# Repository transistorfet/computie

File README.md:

Computie68k
===========

###### *Started October 03, 2019*

Computie is a series of single board computers using the 68010 and 68030 CPUs, along with a simple unix-like
operating system written in C, with preemptive multitasking via a timer interrupt provided by the 68681
serial port controller that is common to all boards.

k30-SBC is the newest board, using a surface-mount 68030 CPU, 2MB of Static RAM, 512KB of Flash for the boot
software and monitor program, and a CompactFlash slot.

68k-SBC is a single board computer with a 68010 CPU, 1MB SRAM, 1MB Flash, and a 68681 Dual UART controller.

68k-SMT is a mostly identical design using SMT and PLCC components.  A CompactFlash card slot has been added
to this version, but it is also possible to connect a simple breadboarded version to 68k-SBC.

For more details on how I got up and running, check out [Bootstrapping a Homebuilt Computer Using An Arduino](https://transistorfet.github.io/posts/2021-09-bootstrapping_with_arduino.html)

For instructions on getting a board set up and software compiled, check out [INSTALL.md](https://github.com/transistorfet/computie/blob/main/INSTALL.md)

This repository uses git submodules, and can be cloned using:
```
git clone --recurse-submodules git@github.com:transistorfet/computie.git
```

ComputieVME - The Next Generation
---------------------------------

The next iteration of this project is ComputieVME, a VME-based MC68030 CPU card, which is part of
the [Retroverse](https://github.com/transistorfet/retroverse/) project, along with a number of other
VME-based components.  The new system also runs the
[Gloworm](https://github.com/transistorfet/gloworm/) operating system.  Development is ongoing and
details can be found in the github repo or at
[jabberwocky.ca](https://jabberwocky.ca/projects/retroverse/).  I also live streamed some of the
designing and building process, with recordings available at
[youtube.com/@transistorfet](https://www.youtube.com/@transistorfet)

The Operating System (Gloworm)
------------------------------

[Gloworm](https://github.com/transistorfet/gloworm/) (now in a separate repository) is largely based on reading
Operating Systems Design and Implementation 2ed by Andrew S. Tanenbaum, although I've gone with a monolithic design, at
least for the time being, for the simplicity of it.  It can do preemptive multitasking using the 68681 timer.  It also
has an implementation of the minix version 1 filesystem, which uses RAM (through a device driver) to store the data, or
a Compact Flash card connected as an IDE device.  The second serial port can be configured as a SLIP device, with a
basic implementation of UDP and TCP through a BSD sockets-style API, and an NTP command is provided for updating the
system time on boot (when booting from disk).

The above video shows connecting over serial from a modern PC and resetting the hardware to run the monitor in ROM
which displays the welcome message.  The kernel is already loaded in RAM, so running the boot command will boot
the kernel which then starts the shell.  From the shell, some basic file operations and the ps command are shown.

The k30 Single Board Computer
-----------------------------

The k30 is the latest version, using a 68030.  It has 2MB SRAM, 512KB Flash, a 68681 Dual UART, and a CompactFlash.
It's as similar to 68k-SMT as possible while still upgrading the CPU.  It doesn't use a programmable logic device for
the glue logic as many similar projects use, instead opting for eleven 74 series logic chips.  It still manages to
use the full 32-bit data bus for RAM, but only one flash chip is used which has an 8-bit data bus in order to reduce
complexity.  Most of the software will be run from RAM, so this shouldn't be a problem.

[k30 Schematics](https://github.com/transistorfet/computie/raw/main/hardware/k30-SBC/k30-SBC.pdf)

DIP switches are used to select the time delay to use for the CompactFlash card (which is interfaced directly to the
CPU), to enable the bus error watchdog timer, and to enable/disable the cache and MMU features.

k30 Revision 2
--------------

This revision fixes the issues of the previous one.  The compact flash card can now be accessed, and the OS is able
to boot entirely from the compact flash card without issue.

k30 Revision 1
--------------

I made a mistake and used the wrong size footprint for the two 74HC253s, which only come in a 16SSOP package and not
the TSSOP package used by the other logic chips.  The footprint used were 4.9 mm wide but should have been 6.2mm.
Luckily I managed to bend the pins under the body of the chips which was enough to get all the pins touching all the
pads.  It was very tricky to solder, and there was a bridge between DS3 and ground which was very difficult to get
unstuck, but it's working now.

I also made a mistake in the DSACK signals used to terminate a memory cycle, specifically for the compact flash card.
The logic was inverted, so the card was inaccessible, and my attempts at fixing it fried the clock, although it might
have just been the crystal.  I set the project aside for a while and then made a new revision.  For details on the
issues, see the [errata](https://github.com/transistorfet/computie/raw/main/hardware/k30-SBC/revisions/k30-SBC-rev1-errata.txt)

The 68k Single Board Computer
-----------------------------

A simple single board computer using a Motorola 68010 CPU, which can connect to a host computer via USB/TTL-Serial.
It has a bus for connecting a supervisor arduino or expansion devices, but it can operate standalone using the onboard
UARTs.  It has 1MB of onboard Flash, 1MB of onboard SRAM, and a 68681 Dual UART chip with GPIO.  Some of the GPIO
pins are wired to 4 general purpose LEDs and 2 general purpose buttons.

[68k Board Schematics](https://github.com/transistorfet/computie/raw/main/hardware/68k-SBC/68kBoard.pdf)

The serial ports require external TTL-to-something conversion and are designed to be used with an FTDI USB-to-Serial
cable or adapter.  Two optional jumpers can be used to supply power to the board from one of the USB ports (only one
should be jumped at a time, and only if the onboard power supply is disconnected).  It typically takes about 365mA at
5V to power.

Two jumpers are provided to select what address the ROM will appear in (either 0x0000 or 0x2000), and whether to enable
onboard DTACK generation for address space 0x0000.  By moving the ROM to 0x2000 and disabling DTACK in 0x0000, a
connected arduino can boot the 68000 directly.

I decided to use discrete 74 Series chips for the glue logic to keep it simple and easy for others to build.  I tried
to minimize the amount of logic chips needed, so it doesn't have a watchdog timer to trigger a bus error when an
unmapped address is accessed.

It's currently clocked at 12MHz, although there seems to be an issue with the arduino's DTACK generation at that speed.
It previously was working at 10MHz on the rev0 board.

The SBC version uses all DIP packaged chips and through-hole parts.  The SMT version uses surface mount chips for the
logic and ram, and PLCC packaged chips for the rest.  A CompactFlash socket and a 74HC32 to accommodate it has been
added and the power supply has been removed, but it is otherwise the same design.

SMT Revision 1
--------------

SBC Revision 2
--------------

SBC Revision 0
--------------

This version has 64KB of EEPROM instead of Flash, and doesn't have onboard interrupt circuitry.  It started off with a
68000 CPU, but that was later upgraded to a 68010 to allow for relocatable interrupt tables when using off-board
interrupt circuitry.

I made a mistake and left out the logic for LDS/UDS in the chip select for the high and low memory chips.  When writing
a single byte to memory, it would also attempt to write to both the high and low chips, instead of only one.  Thanks to
a poster on EEVblog who suggested patching it with a P-channel MOSFET shown soldered to the back of the SRAM chips to
interpose the UDS/LDS signals into the chip selects, with the original traces cut.

Breadboard Version
------------------

Operating System Booting From Monitor/Compact Flash on 68k-SMT
--------------------------------------------------------------

The above video shows connecting over serial from a modern computer after first powering the board on.  The monitor
runs first, giving the ">" prompt.  The bootloader has been burnt into flash at address 0x20000.  From the monitor, the
boot loader is run, which then loads the kernel from the attached compact flash card.  Each period (.) character
printed represents 1 kilobyte of data loaded from disk).  The boot loader then jumps to the loaded kernel, which
displays boot messages before running the init process from disk.  The init process first runs `sh /etc/rc`", which runs
the ntpdate command to update the system time.  It then runs an interactive shell.

Some commands are shown after boot, and then the httpd program is run (which has forking disabled for the time being).
From another computer, the curl command is run to issue a request to the board.  The httpd program responds with the
data "This is a secret message"

References
----------

- [S-100 68000 CPU Board](http://s100computers.com/My%20System%20Pages/68000%20Board/68K%20CPU%20Board.htm)
- [Tiny68K, 68000 SBC](https://www.retrobrewcomputers.org/doku.php?id=boards:sbc:tiny68k)
- [Motorola 68000 computer](https://hackaday.io/project/7242-motorola-68000-computer)
- [68k Single Board Computer](https://www.kswichit.com/68k/68k.html)
- [Kiwi - a 68k Homebrew Computer](https://www.ist-schlau.de/hardware.html)

- [ECB KISS-68030](https://www.retrobrewcomputers.org/doku.php?id=boards:ecb:kiss-68030:start)
- [Gryphon 68030](https://www.retrobrewcomputers.org/doku.php?id=boards:sbc:gryphon_68030:start)
- [T030](https://hackaday.io/project/9439-t030)
- [Building a 68030 computer in 5 stages](https://hackaday.io/project/164041-building-a-68030-computer-in-5-stages)
- [Blitz - 32bit 68030 homebrew with an ISA bus](https://blog.notartyoms-box.net/blitz/)

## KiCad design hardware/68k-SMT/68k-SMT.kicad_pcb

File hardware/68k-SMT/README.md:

68k-SMT
=======

Status: Built & Tested

Latest: Rev.1

### About
This is an almost identical version as the 68k-SBC Rev.2 but using either PLCC chips or surface
mount chips, and with the addition of a CompactFlash card slot.  This was the first board I made
with surface mount chips, and I pushed myself a bit with the TSSOP logic chips, which were the
hardest to solder.  The CompactFlash socket was the easiest to solder because it has holes that
aligned the pins with the pad perfectly.  I also had issues with taking too much solder off the
memory chips causing micro-fractures in the solder that resulted in crashing/locking up.

The goal here was to learn surface mount soldering techniques so that I could attempt a 68030 based
design.  I had lots of $10 QFP package 68030s, but the PGA packages were about 4 times the price,
plus about $10 CAD including shipping and duties for a PGA socket (which is this [128-pin 13x13 PGA
socket](https://www.peconnectors.com/sockets-pga-cpu-and-memory/hws4514/)

[Revision 1 Notes & Errata](revisions/68k-SMT-rev1-errata.txt)

[Revision 1 Schematic](revisions/68k-SMT-rev1.pdf)

[Revision 1 Gerbers](revisions/68k-SMT-rev1.zip)

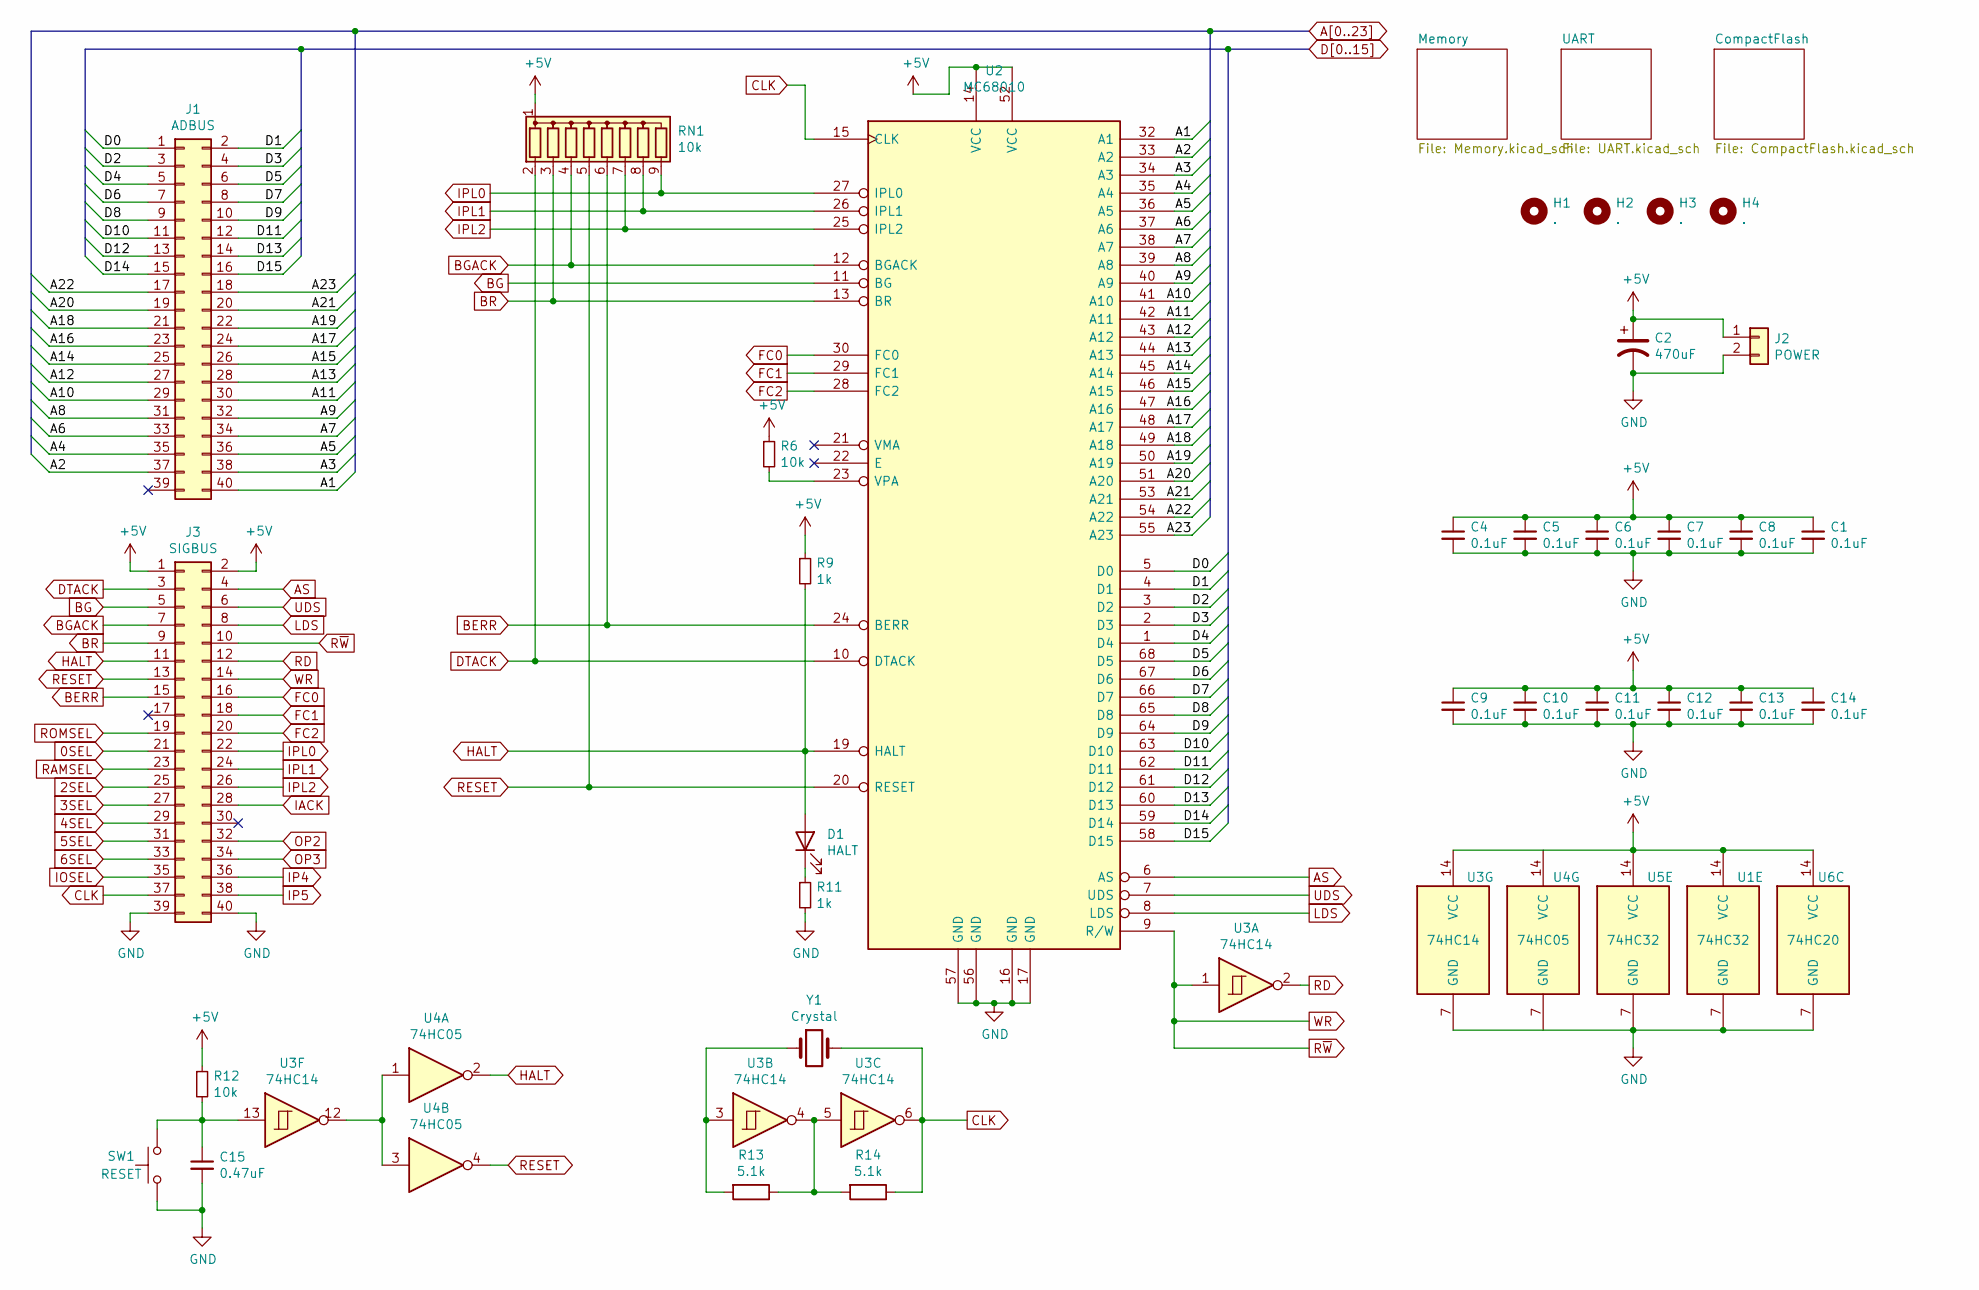
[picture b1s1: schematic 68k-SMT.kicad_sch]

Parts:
C1, C4, C5, C6, C7, C8, C9, C10, C11, C12, C13, C14: 0.1uF; C_Disc_D3.0mm_W2.0mm_P2.50mm
C2: 470uF; CP_Radial_D10.0mm_P5.00mm
C15: 0.47uF; C_Disc_D3.0mm_W2.0mm_P2.50mm
D1: HALT; LED_D5.0mm
H1, H2, H3, H4: .; MountingHole_2.7mm_Pad_Via
J1: ADBUS; PinHeader_2x20_P2.54mm_Vertical
J2: POWER; PinHeader_1x02_P2.54mm_Vertical
J3: SIGBUS; PinHeader_2x20_P2.54mm_Vertical
R6, R12: 10k; R_Axial_DIN0204_L3.6mm_D1.6mm_P5.08mm_Horizontal
R9, R11: 1k; R_Axial_DIN0204_L3.6mm_D1.6mm_P5.08mm_Horizontal
R13, R14: 5.1k; R_Axial_DIN0204_L3.6mm_D1.6mm_P5.08mm_Horizontal
RN1: 10k; R_Array_SIP9
SW1: RESET; SW_PUSH_6mm
U1, U5: 74HC32; TSSOP-14_4.4x5mm_P0.65mm
U2: MC68010; PLCC-68_THT-Socket
U3: 74HC14; TSSOP-14_4.4x5mm_P0.65mm
U4: 74HC05; TSSOP-14_4.4x5mm_P0.65mm
U6: 74HC20; TSSOP-14_4.4x5mm_P0.65mm
Y1: Crystal; Crystal_HC49-4H_Vertical

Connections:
0SEL: J3.21; also elsewhere on the board
2SEL: J3.25; also elsewhere on the board
3SEL: J3.27; also elsewhere on the board
4SEL: J3.29; also elsewhere on the board
5SEL: J3.31; also elsewhere on the board
6SEL: J3.33; also elsewhere on the board
+5V: C1.1, C2.1, C4.1, C5.1, C6.1, C7.1, C8.1, C9.1, C10.1, C11.1, C12.1, C13.1, C14.1, J2.1, J3.1, J3.2, R6.1, R9.1, R12.1, RN1.1 (common), U1.14 (VCC), U2.14 (VCC), U2.52 (VCC), U3.14 (VCC), U4.14 (VCC), U5.14 (VCC), U6.14 (VCC); also elsewhere on the board
A1: J1.40, U2.32 (A1); also elsewhere on the board
A2: J1.37, U2.33 (A2); also elsewhere on the board
A3: J1.38, U2.34 (A3); also elsewhere on the board
A4: J1.35, U2.35 (A4); also elsewhere on the board
A5: J1.36, U2.36 (A5); also elsewhere on the board
A6: J1.33, U2.37 (A6); also elsewhere on the board
A7: J1.34, U2.38 (A7); also elsewhere on the board
A8: J1.31, U2.39 (A8); also elsewhere on the board
A9: J1.32, U2.40 (A9); also elsewhere on the board
A10: J1.29, U2.41 (A10); also elsewhere on the board
A11: J1.30, U2.42 (A11); also elsewhere on the board
A12: J1.27, U2.43 (A12); also elsewhere on the board
A13: J1.28, U2.44 (A13); also elsewhere on the board
A14: J1.25, U2.45 (A14); also elsewhere on the board
A15: J1.26, U2.46 (A15); also elsewhere on the board
A16: J1.23, U2.47 (A16); also elsewhere on the board
A17: J1.24, U2.48 (A17); also elsewhere on the board
A18: J1.21, U2.49 (A18); also elsewhere on the board
A19: J1.22, U2.50 (A19); also elsewhere on the board
A20: J1.19, U2.51 (A20); also elsewhere on the board
A21: J1.20, U2.53 (A21); also elsewhere on the board
A22: J1.17, U2.54 (A22); also elsewhere on the board
A23: J1.18, U2.55 (A23); also elsewhere on the board
AS: J3.4, U2.6 (AS); also elsewhere on the board
BERR: J3.15, RN1.6 (R5), U2.24 (BERR)
BG: J3.5, U2.11 (BG)
BGACK: J3.7, RN1.4 (R3), U2.12 (BGACK)
BR: J3.9, RN1.3 (R2), U2.13 (BR)
CLK: J3.37, R14.1, U2.15 (CLK), U3.6, Y1.2
D0: J1.1, U2.5 (D0); also elsewhere on the board
D1: J1.2, U2.4 (D1); also elsewhere on the board
D2: J1.3, U2.3 (D2); also elsewhere on the board
D3: J1.4, U2.2 (D3); also elsewhere on the board
D4: J1.5, U2.1 (D4); also elsewhere on the board
D5: J1.6, U2.68 (D5); also elsewhere on the board
D6: J1.7, U2.67 (D6); also elsewhere on the board
D7: J1.8, U2.66 (D7); also elsewhere on the board
D8: J1.9, U2.65 (D8); also elsewhere on the board
D9: J1.10, U2.64 (D9); also elsewhere on the board
D10: J1.11, U2.63 (D10); also elsewhere on the board
D11: J1.12, U2.62 (D11); also elsewhere on the board
D12: J1.13, U2.61 (D12); also elsewhere on the board
D13: J1.14, U2.60 (D13); also elsewhere on the board
D14: J1.15, U2.59 (D14); also elsewhere on the board
D15: J1.16, U2.58 (D15); also elsewhere on the board
DTACK: J3.3, RN1.2 (R1), U2.10 (DTACK); also elsewhere on the board
FC0: J3.16, U2.30 (FC0); also elsewhere on the board
FC1: J3.18, U2.29 (FC1); also elsewhere on the board
FC2: J3.20, U2.28 (FC2); also elsewhere on the board
GND: C1.2, C2.2, C4.2, C5.2, C6.2, C7.2, C8.2, C9.2, C10.2, C11.2, C12.2, C13.2, C14.2, C15.2, J2.2, J3.39, J3.40, R11.2, SW1.1, U1.7 (GND), U2.16 (GND), U2.17 (GND), U2.56 (GND), U2.57 (GND), U3.7 (GND), U4.7 (GND), U5.7 (GND), U6.7 (GND); also elsewhere on the board
HALT: D1.2 (A), J3.11, R9.2, U2.19 (HALT), U4.2
IACK: J3.28; also elsewhere on the board
IOSEL: J3.35; also elsewhere on the board
IP4: J3.36; also elsewhere on the board
IP5: J3.38; also elsewhere on the board
IPL0: J3.22, RN1.9 (R8), U2.27 (IPL0)
IPL1: J3.24, RN1.8 (R7), U2.26 (IPL1); also elsewhere on the board
IPL2: J3.26, RN1.7 (R6), U2.25 (IPL2)
LDS: J3.8, U2.8 (LDS); also elsewhere on the board
unnamed: C15.1, R12.2, SW1.2, U3.13
unnamed: D1.1 (K), R11.1
unnamed: R6.2, U2.23 (VPA)
unnamed: R13.1, R14.2, U3.4, U3.5
unnamed: R13.2, U3.3, Y1.1
unnamed: U3.12, U4.1, U4.3
OP2: J3.32; also elsewhere on the board
OP3: J3.34; also elsewhere on the board
RAMSEL: J3.23; also elsewhere on the board
RD: J3.12, U3.2; also elsewhere on the board
RESET: J3.13, RN1.5 (R4), U2.20 (RESET), U4.4; also elsewhere on the board
ROMSEL: J3.19; also elsewhere on the board
R~W: J3.10, J3.14, U2.9 (R/W), U3.1; also elsewhere on the board
UDS: J3.6, U2.7 (UDS); also elsewhere on the board

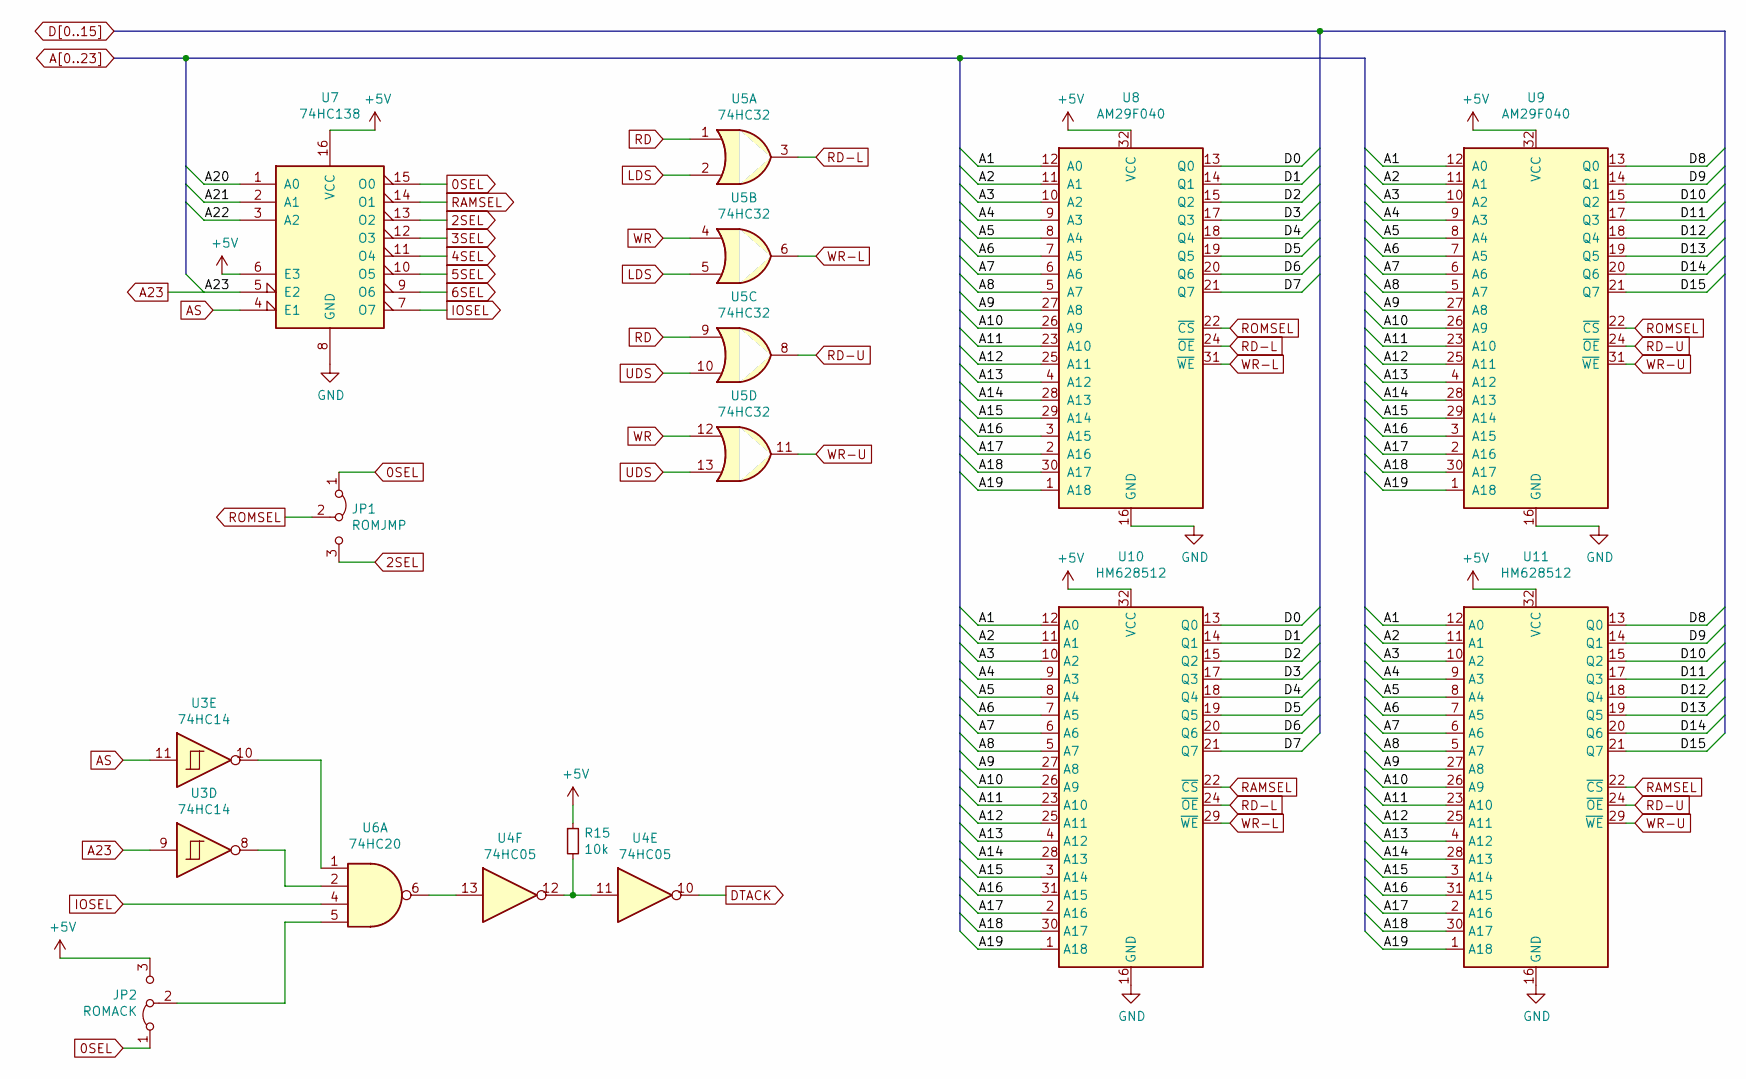
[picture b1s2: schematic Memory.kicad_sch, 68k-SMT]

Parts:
JP1: ROMJMP; PinHeader_1x03_P2.54mm_Vertical
JP2: ROMACK; PinHeader_1x03_P2.54mm_Vertical
R15: 10k; R_Axial_DIN0204_L3.6mm_D1.6mm_P5.08mm_Horizontal
U3: 74HC14; TSSOP-14_4.4x5mm_P0.65mm
U4: 74HC05; TSSOP-14_4.4x5mm_P0.65mm
U5: 74HC32; TSSOP-14_4.4x5mm_P0.65mm
U6: 74HC20; TSSOP-14_4.4x5mm_P0.65mm
U7: 74HC138; TSSOP-16_4.4x5mm_P0.65mm
U8, U9: AM29F040; PLCC-32_THT-Socket
U10, U11: HM628512; TSOP-II-32_21.0x10.2mm_P1.27mm

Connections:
0SEL: JP1.1 (A), JP2.1 (A), U7.15 (O0); also elsewhere on the board
2SEL: JP1.3 (B), U7.13 (O2); also elsewhere on the board
3SEL: U7.12 (O3); also elsewhere on the board
4SEL: U7.11 (O4); also elsewhere on the board
5SEL: U7.10 (O5); also elsewhere on the board
6SEL: U7.9 (O6); also elsewhere on the board
+5V: JP2.3 (B), R15.1, U7.6 (E3), U7.16 (VCC), U8.32 (VCC), U9.32 (VCC), U10.32 (VCC), U11.32 (VCC); also elsewhere on the board
A1: U8.12 (A0), U9.12 (A0), U10.12 (A0), U11.12 (A0); also elsewhere on the board
A2: U8.11 (A1), U9.11 (A1), U10.11 (A1), U11.11 (A1); also elsewhere on the board
A3: U8.10 (A2), U9.10 (A2), U10.10 (A2), U11.10 (A2); also elsewhere on the board
A4: U8.9 (A3), U9.9 (A3), U10.9 (A3), U11.9 (A3); also elsewhere on the board
A5: U8.8 (A4), U9.8 (A4), U10.8 (A4), U11.8 (A4); also elsewhere on the board
A6: U8.7 (A5), U9.7 (A5), U10.7 (A5), U11.7 (A5); also elsewhere on the board
A7: U8.6 (A6), U9.6 (A6), U10.6 (A6), U11.6 (A6); also elsewhere on the board
A8: U8.5 (A7), U9.5 (A7), U10.5 (A7), U11.5 (A7); also elsewhere on the board
A9: U8.27 (A8), U9.27 (A8), U10.27 (A8), U11.27 (A8); also elsewhere on the board
A10: U8.26 (A9), U9.26 (A9), U10.26 (A9), U11.26 (A9); also elsewhere on the board
A11: U8.23 (A10), U9.23 (A10), U10.23 (A10), U11.23 (A10); also elsewhere on the board
A12: U8.25 (A11), U9.25 (A11), U10.25 (A11), U11.25 (A11); also elsewhere on the board
A13: U8.4 (A12), U9.4 (A12), U10.4 (A12), U11.4 (A12); also elsewhere on the board
A14: U8.28 (A13), U9.28 (A13), U10.28 (A13), U11.28 (A13); also elsewhere on the board
A15: U8.29 (A14), U9.29 (A14), U10.3 (A14), U11.3 (A14); also elsewhere on the board
A16: U8.3 (A15), U9.3 (A15), U10.31 (A15), U11.31 (A15); also elsewhere on the board
A17: U8.2 (A16), U9.2 (A16), U10.2 (A16), U11.2 (A16); also elsewhere on the board
A18: U8.30 (A17), U9.30 (A17), U10.30 (A17), U11.30 (A17); also elsewhere on the board
A19: U8.1 (A18), U9.1 (A18), U10.1 (A18), U11.1 (A18); also elsewhere on the board
A20: U7.1 (A0); also elsewhere on the board
A21: U7.2 (A1); also elsewhere on the board
A22: U7.3 (A2); also elsewhere on the board
A23: U3.9, U7.5 (E2); also elsewhere on the board
AS: U3.11, U7.4 (E1); also elsewhere on the board
D0: U8.13 (Q0), U10.13 (Q0); also elsewhere on the board
D1: U8.14 (Q1), U10.14 (Q1); also elsewhere on the board
D2: U8.15 (Q2), U10.15 (Q2); also elsewhere on the board
D3: U8.17 (Q3), U10.17 (Q3); also elsewhere on the board
D4: U8.18 (Q4), U10.18 (Q4); also elsewhere on the board
D5: U8.19 (Q5), U10.19 (Q5); also elsewhere on the board
D6: U8.20 (Q6), U10.20 (Q6); also elsewhere on the board
D7: U8.21 (Q7), U10.21 (Q7); also elsewhere on the board
D8: U9.13 (Q0), U11.13 (Q0); also elsewhere on the board
D9: U9.14 (Q1), U11.14 (Q1); also elsewhere on the board
D10: U9.15 (Q2), U11.15 (Q2); also elsewhere on the board
D11: U9.17 (Q3), U11.17 (Q3); also elsewhere on the board
D12: U9.18 (Q4), U11.18 (Q4); also elsewhere on the board
D13: U9.19 (Q5), U11.19 (Q5); also elsewhere on the board
D14: U9.20 (Q6), U11.20 (Q6); also elsewhere on the board
D15: U9.21 (Q7), U11.21 (Q7); also elsewhere on the board
DTACK: U4.10; also elsewhere on the board
GND: U7.8 (GND), U8.16 (GND), U9.16 (GND), U10.16 (GND), U11.16 (GND); also elsewhere on the board
IOSEL: U6.4, U7.7 (O7); also elsewhere on the board
LDS: U5.2, U5.5; also elsewhere on the board
unnamed: JP2.2 (C), U6.5
unnamed: R15.2, U4.11, U4.12
unnamed: U3.8, U6.2
unnamed: U3.10, U6.1
unnamed: U4.13, U6.6
RAMSEL: U7.14 (O1), U10.22 (~CS), U11.22 (~CS); also elsewhere on the board
RD: U5.1, U5.9; also elsewhere on the board
RD-L: U5.3, U8.24 (~OE), U10.24 (~OE)
RD-U: U5.8, U9.24 (~OE), U11.24 (~OE)
ROMSEL: JP1.2 (C), U8.22 (~CS), U9.22 (~CS); also elsewhere on the board
R~W: U5.4, U5.12; also elsewhere on the board
UDS: U5.10, U5.13; also elsewhere on the board
WR-L: U5.6, U8.31 (~WE), U10.29 (~WE)
WR-U: U5.11, U9.31 (~WE), U11.29 (~WE)

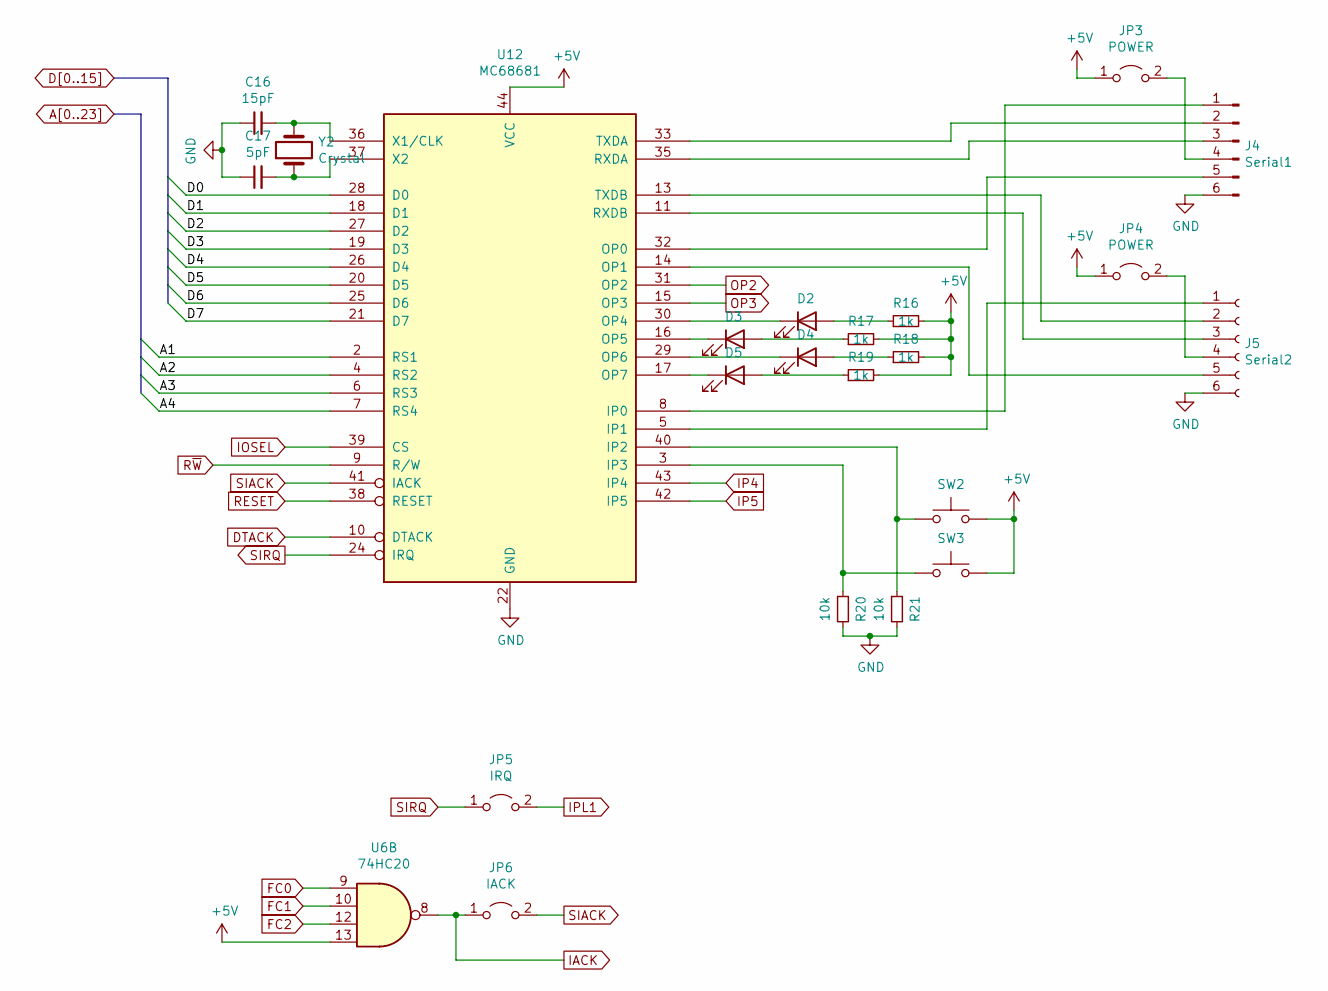
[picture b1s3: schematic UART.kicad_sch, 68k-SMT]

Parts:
C16: 15pF; C_Disc_D3.0mm_W2.0mm_P2.50mm
C17: 5pF; C_Disc_D3.0mm_W2.0mm_P2.50mm
D2: OP4; LED_D5.0mm
D3: OP5; LED_D5.0mm
D4: OP6; LED_D5.0mm
D5: OP7; LED_D5.0mm
J4: Serial1; PinHeader_1x06_P2.54mm_Horizontal
J5: Serial2; PinHeader_1x06_P2.54mm_Horizontal
JP3, JP4: POWER; PinHeader_1x02_P2.54mm_Vertical
JP5: IRQ; PinHeader_1x02_P2.54mm_Vertical
JP6: IACK; PinHeader_1x02_P2.54mm_Vertical
R16, R17, R18, R19: 1k; R_Axial_DIN0204_L3.6mm_D1.6mm_P5.08mm_Horizontal
R20, R21: 10k; R_Axial_DIN0204_L3.6mm_D1.6mm_P5.08mm_Horizontal
SW2: IP2; SW_PUSH_6mm
SW3: IP3; SW_PUSH_6mm
U6: 74HC20; TSSOP-14_4.4x5mm_P0.65mm
U12: MC68681; PLCC-68_THT-Socket
Y2: Crystal; Crystal_HC49-4H_Vertical

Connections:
+5V: JP3.1 (A), JP4.1 (A), R16.2, R17.2, R18.2, R19.2, SW2.2, SW3.2, U6.13, U12.44 (VCC); also elsewhere on the board
A1: U12.2 (RS1); also elsewhere on the board
A2: U12.4 (RS2); also elsewhere on the board
A3: U12.6 (RS3); also elsewhere on the board
A4: U12.7 (RS4); also elsewhere on the board
D0: U12.28 (D0); also elsewhere on the board
D1: U12.18 (D1); also elsewhere on the board
D2: U12.27 (D2); also elsewhere on the board
D3: U12.19 (D3); also elsewhere on the board
D4: U12.26 (D4); also elsewhere on the board
D5: U12.20 (D5); also elsewhere on the board
D6: U12.25 (D6); also elsewhere on the board
D7: U12.21 (D7); also elsewhere on the board
DTACK: U12.10 (DTACK); also elsewhere on the board
FC0: U6.9; also elsewhere on the board
FC1: U6.10; also elsewhere on the board
FC2: U6.12; also elsewhere on the board
GND: C16.1, C17.1, J4.6, J5.6, R20.2, R21.2, U12.22 (GND); also elsewhere on the board
IACK: JP6.1 (A), U6.8; also elsewhere on the board
IOSEL: U12.39 (CS); also elsewhere on the board
IP4: U12.43 (IP4); also elsewhere on the board
IP5: U12.42 (IP5); also elsewhere on the board
IPL1: JP5.2 (B); also elsewhere on the board
unnamed: C16.2, U12.36 (X1/CLK), Y2.2
unnamed: C17.2, U12.37 (X2), Y2.1
unnamed: D2.1 (K), U12.30 (OP4)
unnamed: D2.2 (A), R16.1
unnamed: D3.1 (K), U12.16 (OP5)
unnamed: D3.2 (A), R17.1
unnamed: D4.1 (K), U12.29 (OP6)
unnamed: D4.2 (A), R18.1
unnamed: D5.1 (K), U12.17 (OP7)
unnamed: D5.2 (A), R19.1
unnamed: J4.1, U12.8 (IP0)
unnamed: J4.2, U12.33 (TXDA)
unnamed: J4.3, U12.35 (RXDA)
unnamed: J4.4, JP3.2 (B)
unnamed: J4.5, U12.32 (OP0)
unnamed: J5.1, U12.5 (IP1)
unnamed: J5.2, U12.13 (TXDB)
unnamed: J5.3, U12.11 (RXDB)
unnamed: J5.4, JP4.2 (B)
unnamed: J5.5, U12.14 (OP1)
unnamed: R20.1, SW3.1, U12.3 (IP3)
unnamed: R21.1, SW2.1, U12.40 (IP2)
OP2: U12.31 (OP2); also elsewhere on the board
OP3: U12.15 (OP3); also elsewhere on the board
RESET: U12.38 (RESET); also elsewhere on the board
R~W: U12.9 (R/W); also elsewhere on the board
SIACK: JP6.2 (B), U12.41 (IACK)
SIRQ: JP5.1 (A), U12.24 (IRQ)

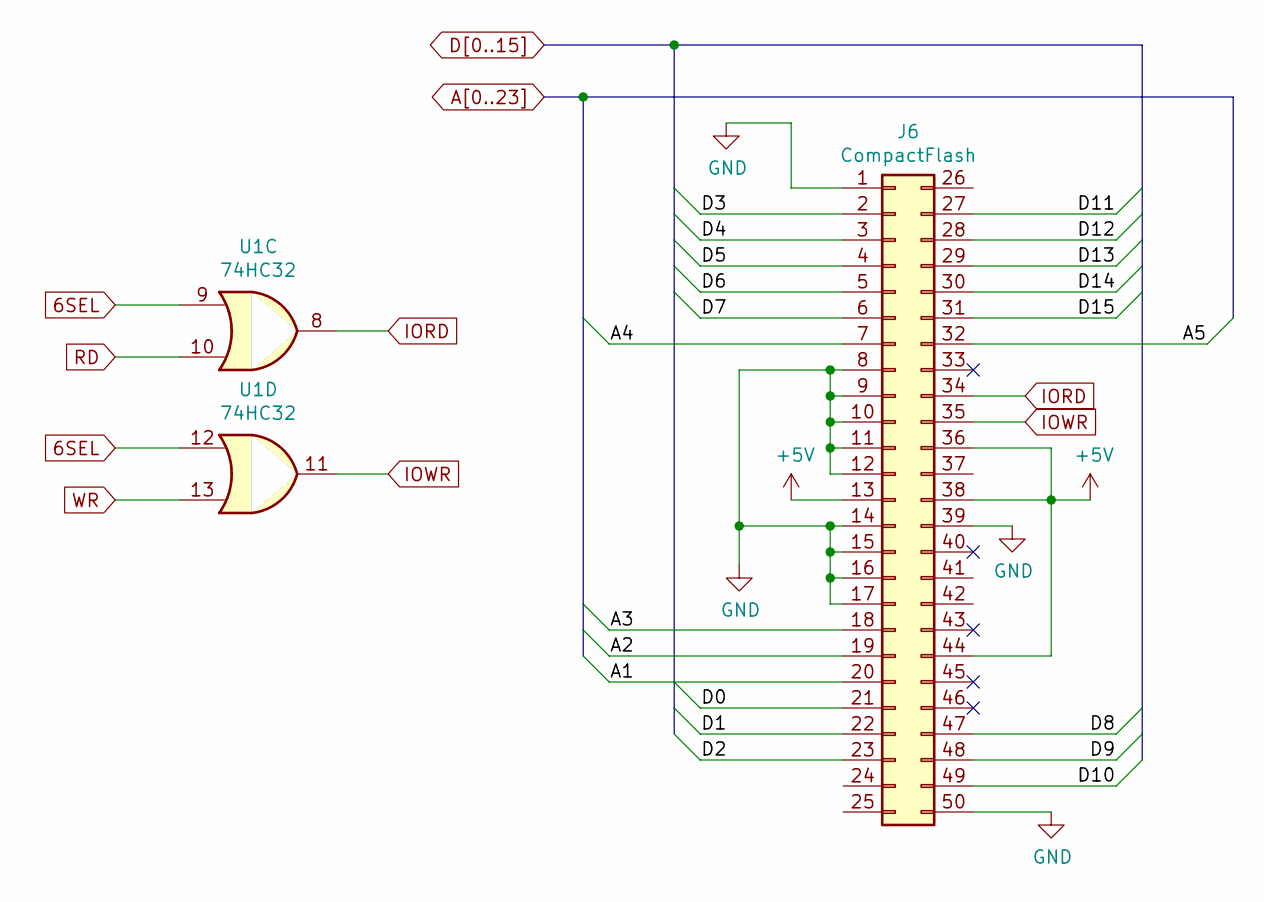
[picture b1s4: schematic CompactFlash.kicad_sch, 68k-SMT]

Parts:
J6: CompactFlash; CF-Card_3M_N7E50-Q516RB-40
U1: 74HC32; TSSOP-14_4.4x5mm_P0.65mm

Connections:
6SEL: U1.9, U1.12; also elsewhere on the board
+5V: J6.13, J6.36, J6.38, J6.44; also elsewhere on the board
A1: J6.20; also elsewhere on the board
A2: J6.19; also elsewhere on the board
A3: J6.18; also elsewhere on the board
A4: J6.7; also elsewhere on the board
A5: J6.32; also elsewhere on the board
D0: J6.21; also elsewhere on the board
D1: J6.22; also elsewhere on the board
D2: J6.23; also elsewhere on the board
D3: J6.2; also elsewhere on the board
D4: J6.3; also elsewhere on the board
D5: J6.4; also elsewhere on the board
D6: J6.5; also elsewhere on the board
D7: J6.6; also elsewhere on the board
D8: J6.47; also elsewhere on the board
D9: J6.48; also elsewhere on the board
D10: J6.49; also elsewhere on the board
D11: J6.27; also elsewhere on the board
D12: J6.28; also elsewhere on the board
D13: J6.29; also elsewhere on the board
D14: J6.30; also elsewhere on the board
D15: J6.31; also elsewhere on the board
GND: J6.1, J6.8, J6.9, J6.10, J6.11, J6.12, J6.14, J6.15, J6.16, J6.17, J6.39, J6.50; also elsewhere on the board
IORD: J6.34, U1.8
IOWR: J6.35, U1.11
RD: U1.10; also elsewhere on the board
R~W: U1.13; also elsewhere on the board

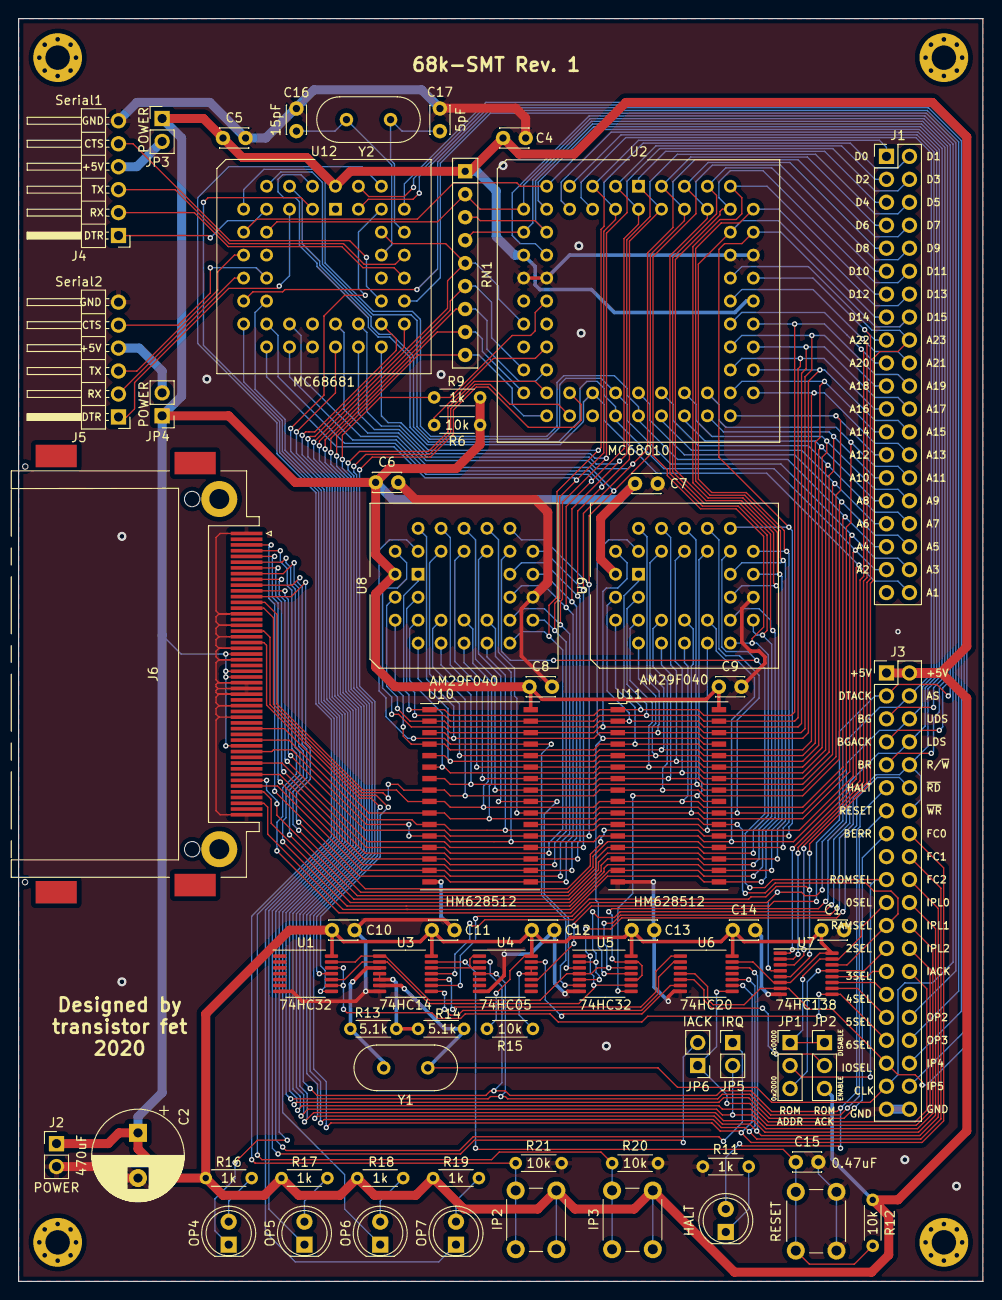
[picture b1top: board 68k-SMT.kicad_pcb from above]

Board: 2 copper layers, 106.7 x 139.7 mm, 68 parts (0 on the bottom side), 115 nets.
